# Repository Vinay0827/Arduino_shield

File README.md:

# Arduino Uno Sensor Shield

## Overview
This repository contains the design files for an Arduino Uno Sensor Shield developed as a college project. The shield allows for the simultaneous connection of six sensor modules to an Arduino Uno board, enhancing its functionality for various applications.

## Sensor Modules
The shield supports the following sensor modules:
1. IR Sensor
2. pH Sensor
3. Ultrasonic Sensor
4. Temperature Sensor
5. LCD Module
6. Touch Sensor

## Software Used
The design of the Arduino Uno Sensor Shield was created using KiCad, an open-source electronic design automation (EDA) software suite. KiCad provides a powerful platform for schematic capture, PCB layout, and design rule checking.

## Repository Contents
- `schematic`: Contains the schematic files for the Arduino Uno Sensor Shield.
- `pcb_layout`: Includes the PCB layout files for the shield design.
- `gerber_files`: Contains the Gerber files necessary for PCB fabrication.
- `3d_models`: Includes 3D models of the shield for visualization purposes.

## How to Use
To use the Arduino Uno Sensor Shield:
1. Download the design files from this repository.
2. Open the schematic and PCB layout files in KiCad.
3. Review the design and make any necessary modifications.
4. Generate Gerber files for PCB fabrication.
5. Fabricate the PCB and assemble the components according to the provided layout.
6. Connect the Arduino Uno board to the sensor shield.
7. Connect the desired sensor modules to the shield's headers.
8. Upload the appropriate firmware to the Arduino Uno board.
9. Test the functionality of the sensor shield with the connected sensor modules.

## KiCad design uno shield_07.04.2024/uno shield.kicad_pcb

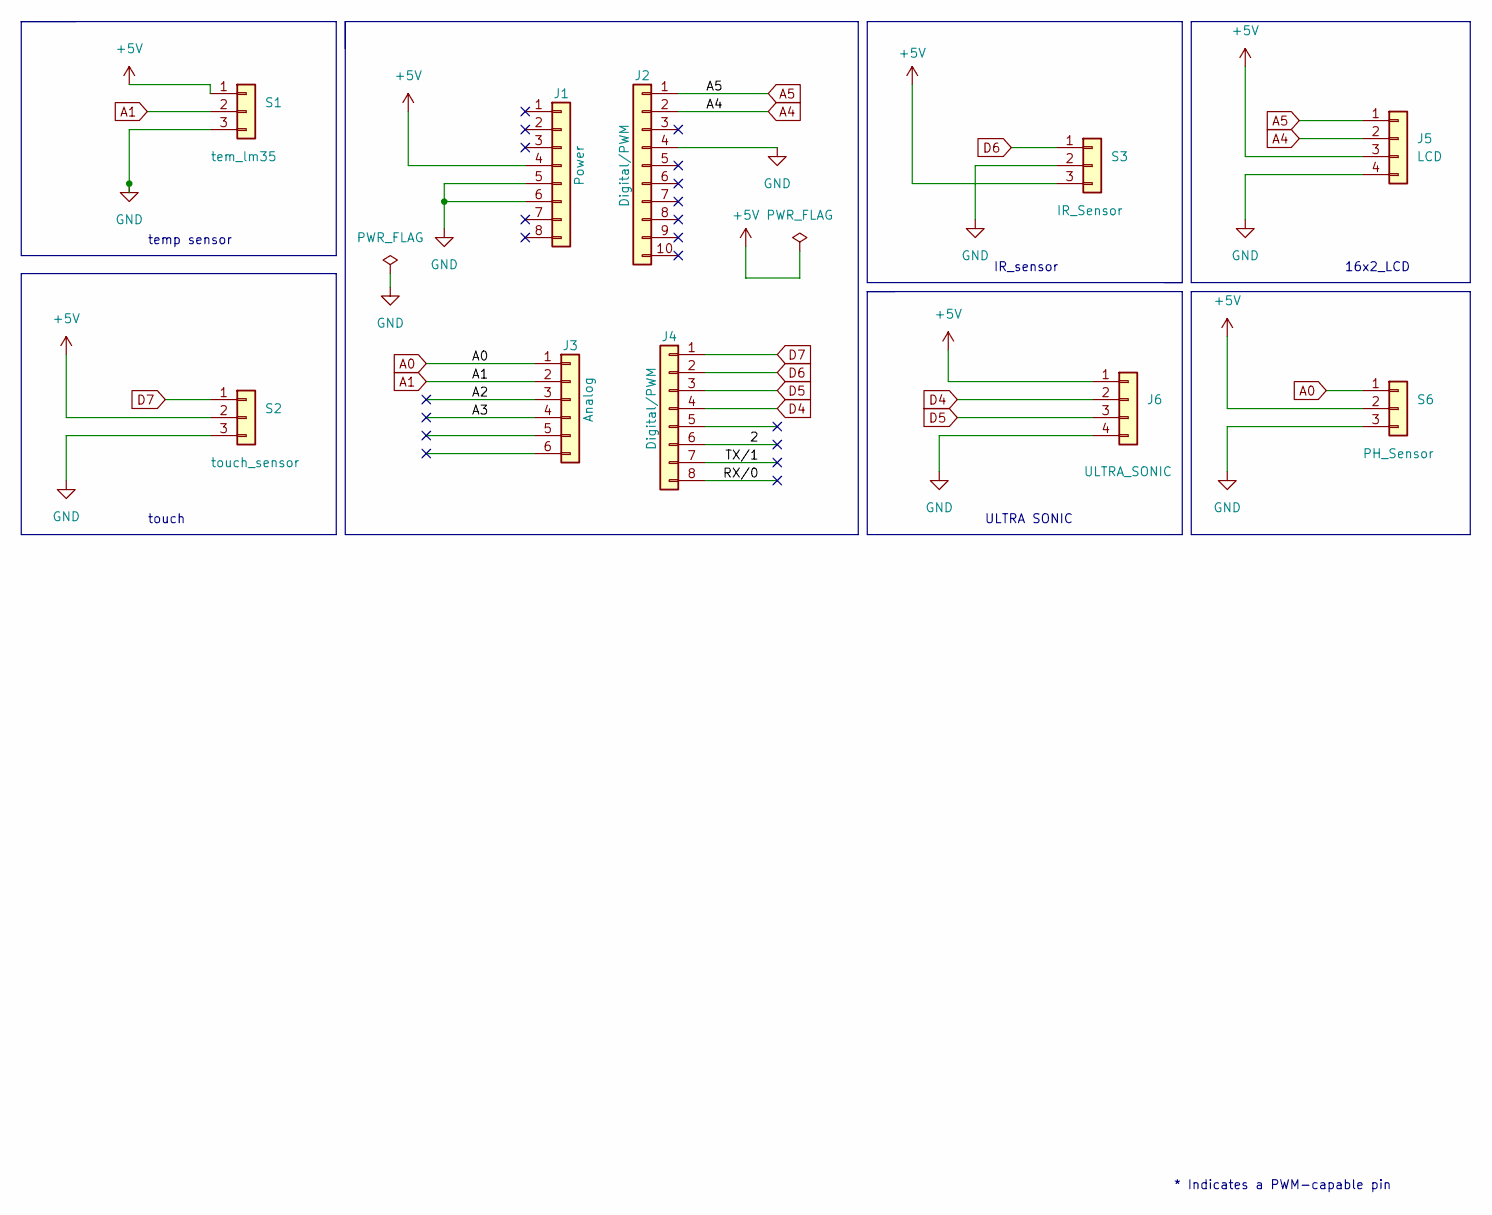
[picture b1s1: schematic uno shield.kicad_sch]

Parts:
J1: Power; PinSocket_1x08_P2.54mm_Vertical
J2: Digital/PWM; PinSocket_1x10_P2.54mm_Vertical
J3: Analog; PinSocket_1x06_P2.54mm_Vertical
J4: Digital/PWM; PinSocket_1x08_P2.54mm_Vertical
J5: LCD; PinSocket_1x04_P2.54mm_Vertical
J6: ULTRA_SONIC; PinSocket_1x04_P2.54mm_Vertical
S1: tem_lm35; PinSocket_1x03_P2.54mm_Vertical
S2: touch_sensor; PinSocket_1x03_P2.54mm_Vertical
S3: IR_Sensor; PinSocket_1x03_P2.54mm_Vertical
S6: PH_Sensor; PinSocket_1x03_P2.54mm_Vertical

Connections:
+5V: J1.4, J5.3, J6.1, S1.1, S2.2, S3.3, S6.2
/2: J4.6
/A2: J3.3
/A3: J3.4
/RX/0: J4.8
/TX/1: J4.7
A0: J3.1, S6.1
A1: J3.2, S1.2
A4: J2.2, J5.2
A5: J2.1, J5.1
D4: J4.4, J6.2
D5: J4.3, J6.3
D6: J4.2, S3.1
D7: J4.1, S2.1
GND: J1.5, J1.6, J2.4, J5.4, J6.4, S1.3, S2.3, S3.2, S6.3

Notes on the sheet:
ULTRA SONIC
IR_sensor
temp sensor
16x2_LCD
touch
* Indicates a PWM-capable pin

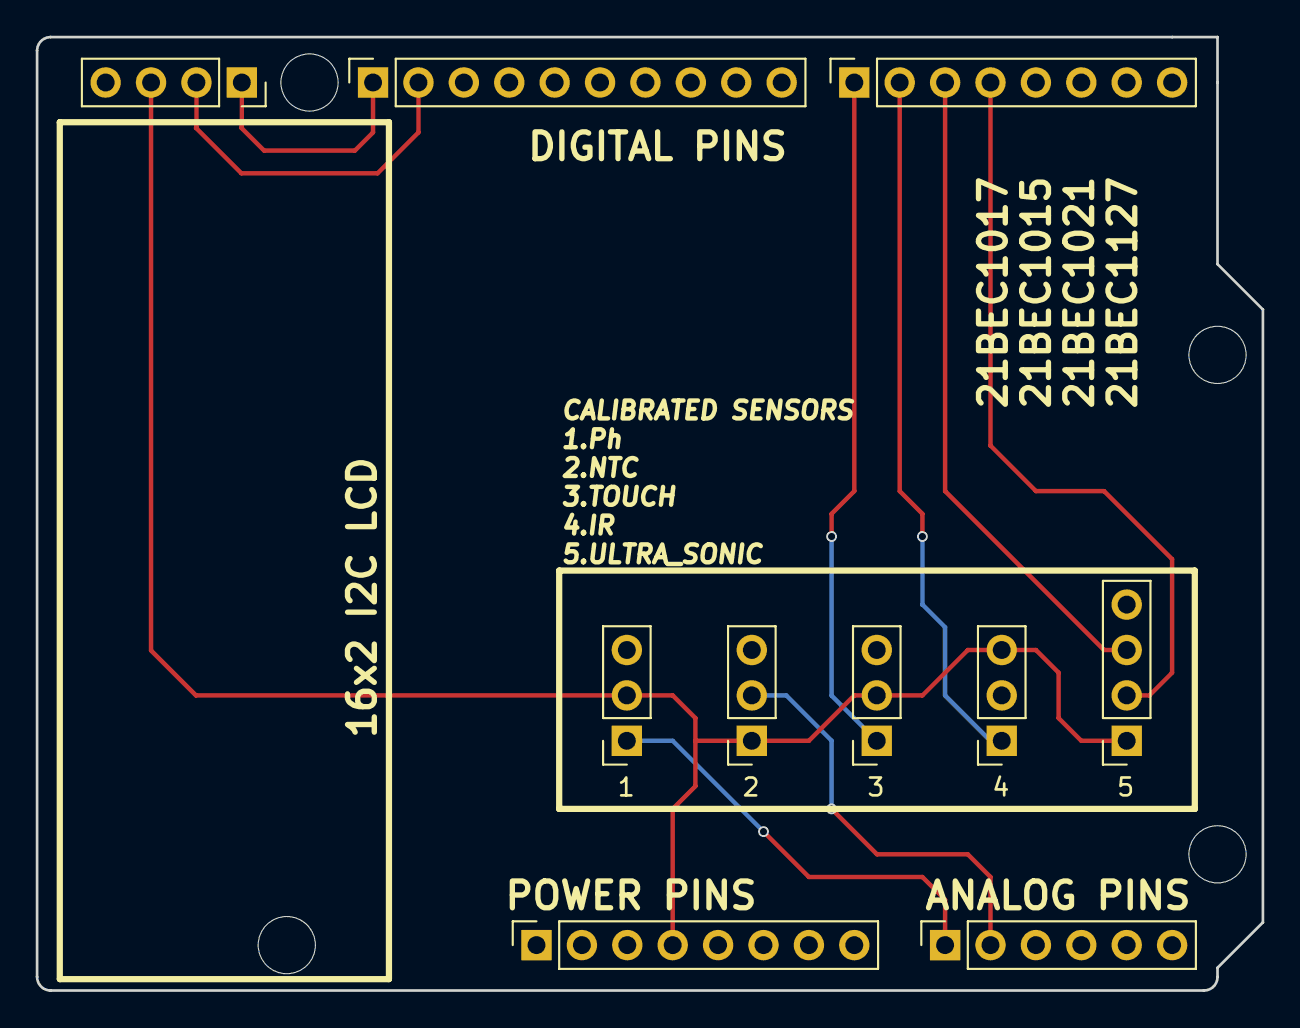
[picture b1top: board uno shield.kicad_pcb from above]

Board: 2 copper layers, 68.6 x 53.3 mm, 14 parts (0 on the bottom side), 10 nets.

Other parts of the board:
MH1, MH2, MH3, MH4: MountingHole_3.2mm
